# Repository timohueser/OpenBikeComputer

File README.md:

<div align="center">

# OpenBikeComputer

**An open-source GPS computer for bikepacking.**

[Live browser demo](https://openbikecomputer.com/#demo) ·
[Documentation](https://openbikecomputer.com/docs/software/architecture/) ·
[Contributing](.github/CONTRIBUTING.md)

</div>

> [!NOTE]
> This project is developed with extensive use of AI coding tools. Don't get out your "AI Slop"
> pitchforks just yet though. Any text you read in the software or documentation that sounds AI
> generated will be replaced once we get closer to releasing this project. The goal is that all
> user-facing text is 100% human-generated!

OpenBikeComputer is a fully open-source, bikepacking-focused GPS cycling computer.
The main features and capabilities we are aiming for are the following (roughly in order of importance):
- Reliable and simple map-based tracking and navigation
- Uploading a route from the companion app should work every time (no BLE connection issues, no unreasonably low limit on point count in GPX files etc.)
- No subscriptions or accounts required for any of the features of the device
- Long battery life, ideally 4+ days between recharges, if you need to recharge it should work reliably with dynamo hubs that provide 5V
- Helps you keep your phone in your pocket by providing all the info you frequently check on the bike:
    - POIS (Shops, water sources, campsites etc.) near you and along the route (including opening hours), with the ability to create a route there on the fly
    - And a fun one: Mountain peaks around you (PeakFinder style)

This repository contains all the software and hardware files needed to build the OBC and the goal is to eventually provide kits that allow you to build the OBC yourself. The project currently is an active prototype, not a finished product and you can read about the progress of development in our [Blog](https://openbikecomputer.com/blog/). Here are some peeks at the software and hardware designs:

<table>
  <tr>
    <td align="center" width="33%">
      
    </td>
    <td align="center" width="33%">
      
    </td>
    <td align="center" width="33%">
      
    </td>
  </tr>
  <tr>
    <td align="center"><sub>Follow the route on the offline map.</sub></td>
    <td align="center"><sub>Read your ride data as you go.</sub></td>
    <td align="center"><sub>See the climb ahead of you.</sub></td>
  </tr>
  <tr>
    <td align="center" width="33%">
      
    </td>
    <td align="center" width="33%">
      
    </td>
  </tr>
  <tr>
    <td align="center"><sub>Identify the peaks around you.</sub></td>
    <td align="center"><sub>Find a shop, and when it opens.</sub></td>
  </tr>
</table>

<table>
  <tr>
    <td align="center" width="50%">
      
    </td>
    <td align="center" width="50%">
      
    </td>
  </tr>
  <tr>
    <td align="center"><sub>Send a route to the bike computer.</sub></td>
    <td align="center"><sub>Bring the recorded ride back.</sub></td>
  </tr>
</table>

<table>
  <tr>
    <td align="center">
      
    </td>
  </tr>
  <tr>
    <td align="center"><sub>A concept render of the enclosure.</sub></td>
  </tr>
</table>

<table>
  <tr>
    <td align="center">
      
    </td>
  </tr>
  <tr>
    <td align="center"><sub>Five colourways under consideration.</sub></td>
  </tr>
</table>

## Try the simulator

The simulator is the best way to explore the project without hardware. It runs the real device
application in a desktop window and downloads the map, route, terrain, and ride data for the Grimsel
Pass demo on first use.

Install [Rust](https://rustup.rs/), Git, Python 3.14+, uv 0.8.17+ and just 1.57+:

```sh
git clone https://github.com/timohueser/OpenBikeComputer.git
cd OpenBikeComputer
cargo install just
just sim
```

First builds take a few minutes; fixture downloads are cached. `just --list` lists tasks;
`just --show TASK` shows a recipe. Run `./tools/obc setup` for the `obc` alias and completion.
See the [simulator guide](sim/desktop/README.md) for controls and rendering.

## Roadmap

This is the current direction, not a release schedule.

| Stage | Status |
| --- | --- |
| Shared application, offline maps, routing, ride recording | Available in the simulator and browser demo |
| iOS companion and BLE/USB transfer flows | Working with the development platform |
| nRF54LM20 development-kit prototype with the 240 × 320 reflective display | Running on hardware |
| Custom PCB and enclosure | In development |
| Integrated, field-tested bike computer | Next major milestone |
| Reproducible hardware build, assembly, and flashing guide | Planned when the custom hardware is ready |

## Current development platform

The hardware build uses the Nordic nRF54LM20 development kit and a Sharp LS021B7DD02 240 × 320
reflective memory LCD. It reads maps and routes from microSD and connects to the companion software
over BLE and USB. The custom PCB and enclosure are still under development. KiCad sources are in
[`hardware/`](hardware/README.md); CAD sources for the enclosure follow later.

## Repository layout

| Path | Purpose |
| --- | --- |
| `firmware/` | Device application, rendering, protocols, storage, board image, and bootloader |
| `host/` | Host tools, map bakers, fixtures, and test support |
| `planner/` | Router, build tools, service, search, and tile worker |
| `sim/` | Desktop, web and phone simulators, host core, replay, feeder and benchmarks |
| `builder/` | Web builder, Rust/WASM core, USB transport, presets, and server |
| `companion-ios/` | SwiftUI companion app and shared iOS package |
| `specs/` | Normative binary, wire, and vector contracts |
| `fixtures/` | Scenario registry, source provenance, and fixture builders |
| `data/` | External data sources with their licences, regions, and environments |
| `docs/` | Public documentation, website, and project blog |
| `hardware/` | KiCad schematics, PCB layouts, footprints, and component models |
| `tools/` | The `obc` command, repository tools, and verification console |

`Cargo.toml` lists the root workspace crates. The nRF54L board image,
bootloader, and sensor simulator are standalone Cargo roots. The
[architecture guide](https://openbikecomputer.com/docs/software/architecture/) explains the boundaries.

## Other open bike computers

OpenBikeComputer is not the only open source bike computer project! Here is a (non-exhaustive) list of some other cool ones this project is inspired by:

- [IceNav](https://github.com/jgauchia/IceNav-v3) — an ESP32-based GPS navigator with multi-GNSS
  support and both rendered and vector offline maps.
- [OpenTrailPaper](https://github.com/RaemondBW/OpenTrailPaper) — an ESP32-S3 e-paper computer
  with offline maps, ride recording, and an iOS companion.
- [Pedal Guru](https://github.com/juliannojungle/pedal.guru) — a work-in-progress bike computer
  project for Raspberry Pi, RP2040, and ESP32 platforms.
- [Pi Zero Bikecomputer](https://github.com/hishizuka/pizero_bikecomputer) — a Raspberry Pi GPS
  and ANT+ computer with offline maps, navigation, and FIT ride logging.
- [bike-computer-32](https://github.com/lspr98/bike-computer-32) — a low-cost ESP32-C3 mini-map
  with offline OpenStreetMap data, GNSS positioning, and GPX track overlays.

## Contributing

Contributions are always welcome! This project is in the very early stages and many things are still a little chaotic and not well documented in many areas. Code is written almost exclusively using AI coding agents, but all the hardware design is fully human-powered. Help on that front would be especially appreciated. Please just get in contact with me if you want to contribute.

## License

Software is available under [GPL-3.0-only](LICENSE), except `host/obc-data`, which is MIT OR
Apache-2.0 and depends on no GPL crate. Hardware design sources are available under
[CERN-OHL-S-2.0](hardware/LICENSE). Third-party notices are in
[the notice file](tools/licenses/THIRD-PARTY.md).

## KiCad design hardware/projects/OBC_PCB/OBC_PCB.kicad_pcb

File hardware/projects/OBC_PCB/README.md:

# OBC main board

Open `OBC_PCB.kicad_pro` in KiCad 10. Keep the project library tables with the files.
Run electrical checks from this directory:

```sh
kicad-cli sch erc --format json -o /tmp/obc-erc.json OBC_PCB.kicad_sch
kicad-cli pcb drc --schematic-parity --format json -o /tmp/obc-drc.json OBC_PCB.kicad_pcb
```

## Board GPIO map

This table describes the main PCB. The [firmware README](../../../firmware/obc-fw-nrf54l/README.md)
describes the development kit. Port the firmware pin assignments before running it on this board.
`LCD_*_MCU` is the net between U6 and its source resistor; `LCD_*` continues to J1.

| Device | Pad | GPIO | Signal | Connection |
| --- | --- | --- | --- | --- |
| U6 | 1 | P2.01 | SD_CLK | R9, 33 Ω at U6; fixed SD pin |
| U6 | 2 | P2.02 | SD_D0 | Fixed SD pin |
| U6 | 3 | P2.03 | SD_D2 | Fixed SD pin |
| U6 | 4 | P2.04 | SD_D1 | Fixed SD pin |
| U6 | 5 | P2.05 | SD_CMD | Fixed SD pin |
| U6 | 7 | P1.29 | COM_SOURCE |  |
| U6 | 8 | P1.30 | LCD_R0 | R69, 100 Ω at U6 |
| U6 | 9 | P1.31 | LCD_R1 | R70, 100 Ω at U6 |
| U6 | 10 | P1.00 | BUZZER_PWM |  |
| U6 | 11 | P1.01 | LCD_GSP | R77, 220 Ω at U6 |
| U6 | 12 | P1.02 | LCD_GEN | R78, 220 Ω at U6 |
| U6 | 13 | P1.03 | LCD_BSP | R80, 220 Ω at U6 |
| U6 | 14 | P1.04 | LCD_GCK | R76, 220 Ω at U6 |
| U6 | 15 | P1.05 | LCD_BCK | R75, 100 Ω at U6 |
| U6 | 16 | P1.06 | LCD_G0 | R71, 100 Ω at U6 |
| U6 | 22 | P1.07 | LCD_G1 | R72, 100 Ω at U6 |
| U6 | 23 | P1.08 | LCD_B0 | R73, 100 Ω at U6 |
| U6 | 24 | P1.09 | LCD_B1 | R74, 100 Ω at U6 |
| U6 | 25 | P0.03 | GPS_TXD | UARTE30 RX (module TX) |
| U6 | 26 | P0.04 | BTN_SELECT | GPIO SENSE wake |
| U6 | 27 | P0.06 | BTN_NEXT | GPIO SENSE wake |
| U6 | 28 | P0.07 | BTN_BACK | GPIO SENSE wake |
| U6 | 29 | P0.08 | PMIC_INT |  |
| U6 | 30 | P0.09 | GPS_RXD | UARTE30 TX (module RX) |
| U6 | 39 | P1.15 | BTN_PREV | GPIO SENSE wake |
| U6 | 40 | P1.16 | SDA | TWIM22 data |
| U6 | 41 | P1.18 | SCL | TWIM22 clock pin |
| U6 | 47 | P1.19 | ACC_INT1 | GPIO SENSE wake |
| U6 | 50 | P1.24 | LCD_INTB | R79, 220 Ω at U6 |
| U6 | 52 | P2.00 | SD_D3 | Fixed SD pin |
| U2 | 7 | GPIO0 | DISP_5V_EN |  |
| U2 | 8 | GPIO1 | PMIC_INT |  |
| U2 | 9 | GPIO2 | COM_EN |  |
| U2 | 10 | GPIO3 | LOUD |  |
| U2 | 11 | GPIO4 | DISP_DISCHARGE |  |

Use standard drive for the LCD outputs. Disable NFC through `NFCT.PADCONFIG` before
using GSP and GEN. Keep both low during reset. Set SCL and SDA on the same port.
Configure the crystal load capacitors and the internal DC/DC converter before use.
Program the bootloader through J5 before fitting the display.

For the LCD, measure 10–90% rise and fall times at J1. Target 25 ns or less;
the panel limit is 50 ns. The resistor values are initial values for board testing.
Check the image and GNSS reception while the display refreshes.

See Nordic's [port capabilities](https://docs.nordicsemi.com/r/bundle/ps_nrf54lm20a/page/gpio.html-concept_port_capabilities),
[clock-pin rules](https://docs.nordicsemi.com/r/bundle/ps_nrf54lm20a/page/chapters/pin.html-clock_pins)
and [GPIO electrical specification](https://docs.nordicsemi.com/r/bundle/ps_nrf54lm20a/page/elspec.html-unique_1225635930).

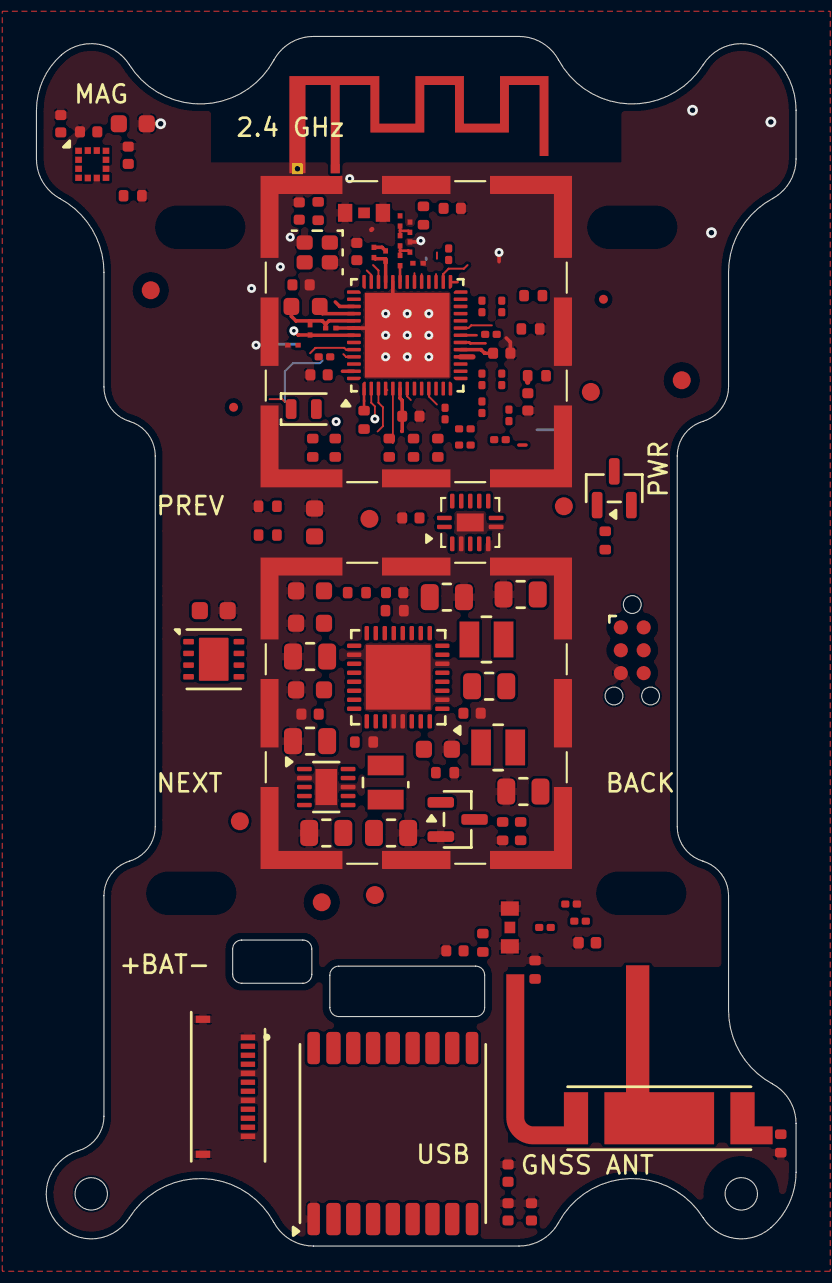
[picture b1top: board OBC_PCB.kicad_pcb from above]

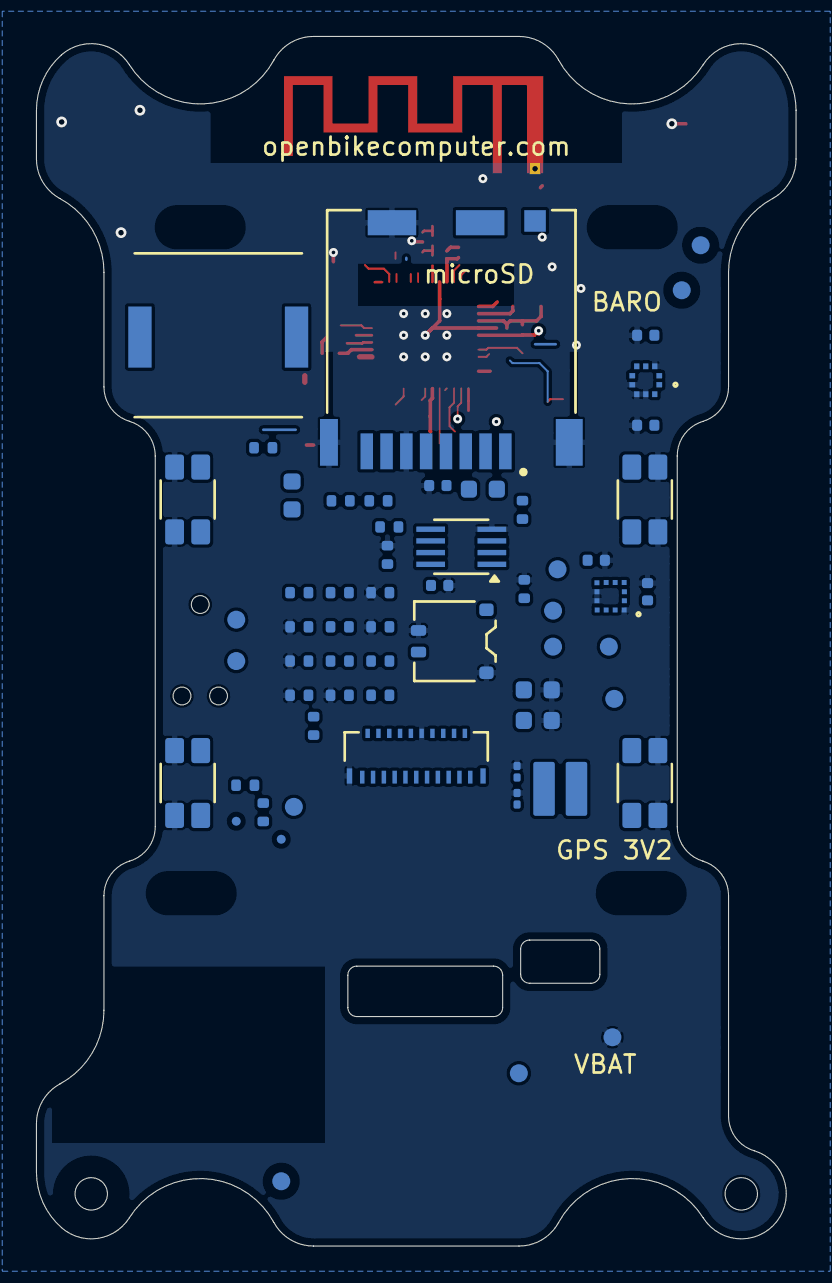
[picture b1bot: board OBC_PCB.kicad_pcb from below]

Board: 8 copper layers, 42.2 x 67.2 mm, 186 parts (61 on the bottom side), 115 nets.

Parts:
AE2: PCB MIFA; Texas_SWRA117D_2.4GHz_Right
ANT1: GGBLA.125.A; Taoglas_GGBLA125A_10x3.2mm_Corner
BZ1: CPT-9019A-SMT-TR
C1, C2, C3, C4, C5, C8: 10u; C_0805_2012Metric
C6, C14, C20, C44, C54: 1u; C_0603_1608Metric
C7, C16, C17, C22, C23, C24, C29, C30, C33, C34, C35, C36, C37, C38, C43, C52, C53: 100n; C_0402_1005Metric
C9, C10: 22u; C_0805_2012Metric
C11, C28: 2.2u; C_0402_1005Metric
C12: 4.7u; C_Nordic_0201_0603Metric
C13: 1p; C_Nordic_0201_0603Metric
C15, C39, C40, C49: 2.2u; C_0603_1608Metric
C21: 10u; C_0402_1005Metric
C25: 2.2u; C_Nordic_0201_0603Metric
C26: 4.7u; C_0402_1005Metric
C27: 10p; C_0201_0603Metric
C31: 47p; C_0201_0603Metric
C32: 4.3p; C_0201_0603Metric
C41, C51: 10u; C_0603_1608Metric
C42: 220n; C_0402_1005Metric
C45: 1.2p; C_Nordic_0201_0603Metric
C46: 1.5p; C_Nordic_0201_0603Metric
C47, C48, C50: tune (C0G); C_0402_1005Metric
C55: 3.9p; C_Nordic_0201_0603Metric
D1: BAS40-7-F; SOT-23
FID1, FID2, FID3, FID4, FID5, FID6: Fiducial_1mm_Mask2mm
FID7, FID8, FID9, FID10: Fiducial_0.5mm_Mask1mm
H1, H2: 1.8mm NPTH
H3, H4, H5, H6: Cradle 4.2x1.6mm NPTH
J1: LS021B7DD02; 5035662102
J2: DM3CS-SF; HRS_DM3CS-SF
J3: FH34SRJ-12S-0.5SH(50); Hirose_FH34SRJ_12S_0.5SH
J4: 1S Li-Po; JST_ACH_2pin
J5: TC2030-CTX-NL; Tag-Connect_TC2030-IDC-NL_2x03_P1.27mm_Vertical
J6: BACKLIGHT A/K - PROVISIONAL SOLDER; Backlight_Flex_Solder_2_P1.8mm_Provisional
J7, J8: RF coax pads; RF_Coax_Solder_GSG
L1, L2, L5: 2.2uH; Wurth_74404024022_2.5x2.0mm
L3: 4.7uH; L_0603_1608Metric
L4: 120R; L_Nordic_0201_0603Metric
L6: 1.0nH; L_Nordic_0201_0603Metric
L7: 3.9nH; L_0402_1005Metric
L8: 3.6nH; L_Nordic_0201_0603Metric
L9: 4.7nH; L_Nordic_0201_0603Metric
L10: 3.3nH; L_Nordic_0201_0603Metric
Q1: AO3400A; SOT-23
R1, R26, R27, R35, R39, R40, R50: 0R; R_0402_1005Metric
R2: 150k; R_0402_1005Metric
R3: 1M; R_0402_1005Metric
R4: 200R; R_0402_1005Metric
R5: 2.2R; R_0402_1005Metric
R9: 33R; R_0402_1005Metric
R20: 10k; R_0402_1005Metric
R23, R24: 4.7k; R_0402_1005Metric
R28, R29, R30, R31, R32, R34, R46: 47k; R_0402_1005Metric
R33, R41, R43: 470R; R_0402_1005Metric
R42, R44, R45, R47, R51, R52, R53, R54, R55, R56, R57, R58, R59, R60, R61, R62, R67: 100k; R_0402_1005Metric
R48, R49: 150R; R_0402_1005Metric
R63: 36.5k; R_0402_1005Metric
R64: 10.5k; R_0201_0603Metric
R65: 36.5k; R_0201_0603Metric
R66: 1k; R_0402_1005Metric
R68: 1k; R_0201_0603Metric
R69, R70, R71, R72, R73, R74, R75: 100; R_0201_0603Metric
R76, R77, R78, R79, R80: 220; R_0201_0603Metric
SH1, SH2: BMI-S-202-F-20-R; Laird_BMI-S-202-F-20_16.5mm
SW1: PREV; TL1016AAF220QG
SW2: NEXT; TL1016AAF220QG
SW3: SELECT / POWER; TL1016AAF220QG
SW4: BACK; TL1016AAF220QG
TP1: SHPHLD; TestPoint_Pad_D1.0mm
TP2: SAFEBOOT; TestPoint_Pad_D1.0mm
TP3: VBAT; TestPoint_Pad_D1.0mm
TP4: VSYS; TestPoint_Pad_D1.0mm
TP5: +3V2; TestPoint_Pad_D1.0mm
TP6: GND; TestPoint_Pad_D1.0mm
TP7: +3V2_GPS; TestPoint_Pad_D1.0mm
TP8: +3V3_SD; TestPoint_Pad_D1.0mm
TP9: COM_SOURCE; TestPoint_Pad_D1.0mm
TP10: +5V_DISP; TestPoint_Pad_D1.0mm
TP11: SCL; TestPoint_Pad_D1.0mm
TP12: SDA; TestPoint_Pad_D1.0mm
TP13: USB_VBUS; TestPoint_Pad_D1.0mm
TP14: VCOM; TestPoint_Pad_D1.0mm
TP15: VA; TestPoint_Pad_D1.0mm
U1: MAX-F11N; ublox_MAX_F11N_Provisional
U2: nPM1300-QEAA; QFN-32-1EP_5x5mm_P0.5mm_EP3.6x3.6mm
U3: BMA400; QFN_BMA400_BOS
U4: LIS2MDL; LGA-12_2x2mm_P0.5mm
U5: BMP581
U6: nRF54LM20A-QGAA; VQFN-52-1EP_6x6mm_P0.4mm_EP4.7x4.7mm
U7: TPS63900DSKR; WSON-10-1EP_2.5x2.5mm_P0.5mm_EP1.2x2mm
U8: SN74LVC02ABQAR; DHWQFN-14-1EP_2.5x3mm_P0.5mm_EP1x1.5mm
U9: LP5810BDSDR; LP5810_DSD0008B
U10: SN74LVC2G00DCTR; SSOP-8_2.95x2.8mm_P0.65mm
Y1: 32MHz; Crystal_SMD_2016-4Pin_2.0x1.6mm
Y3: 32.768kHz; Crystal_SMD_2012-2Pin_2.0x1.2mm

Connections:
+3V2: C2.1, C7.1, C21.1, C22.1, C23.1, C24.1, C30.1, C33.1, C34.1, C35.1, C36.1, C37.1, C38.1, C39.1, C49.1, C51.1, C52.1, C53.1, C54.1, J1.13 (VDD1), J5.1 (VTref), L2.1, R20.1, R23.1, R24.1, TP5.1 (1_1), U1.6 (V_BCKP), U2.12 (VDDIO), U2.30 (LSIN2/VINLDO2), U2.32 (VOUT2), U3.3 (VDDIO), U3.7 (VDD), U3.10 (CSB), U4.3 (~CS), U4.9 (Vdd), U4.10 (Vdd_IO), U5.1 (VDDIO), U5.5 (ADDR), U5.6 (CSB), U5.10 (VDD), U6.6 (VDD), U6.42 (VDD), U6.51 (VDD), U8.14 (VCC), U9.1 (VCC), U10.2, U10.8 (VCC)
+3V2_GPS: C20.1, C28.1, C29.1, TP7.1 (1_1), U1.7 (V_IO), U1.8 (VCC), U2.31 (LSOUT2/VOUTLDO2)
+3V3_SD: C1.1, C41.1, C43.1, J2.4 (VDD), L1.1, R28.1, R29.1, R30.1, R31.1, R32.1, TP8.1 (1_1), U2.1 (VOUT1)
+5V_DISP: C9.1, C10.1, C40.1, J1.21 (VDD2), J6.1, R66.1, TP10.1 (1_1), U7.6 (VOUT)
/ACC_INT1: U3.5 (INT1), U6.47 (P1.19)
/BTN_BACK: SW4.1, U6.28 (P0.07)
/BTN_NEXT: SW2.1, U6.27 (P0.06)
/BTN_PREV: SW1.1, U6.39 (P1.15)
/BTN_SELECT: R43.2, U6.26 (P0.04)
/BUZZER_PWM: R44.1, U6.10 (P1.00), U10.1
/COM_EN: R47.1, U2.9 (GPIO2), U8.5
/COM_SOURCE: R46.1, TP9.1 (1_1), U6.7 (P1.29), U8.2, U8.11
/Display/BL_K: J6.2, U9.8 (OUT0)
/GNSS/GNSS_FTE1: ANT1.2 (FTE), R26.1
/GNSS/GNSS_FTE2: ANT1.3 (FTE), R27.1
/GNSS/GNSS_RF_FEED: ANT1.1, C27.2, L7.1
/GNSS/GNSS_RF_IN: C50.1, R40.1, U1.11 (RF_IN)
/GNSS/GNSS_RF_MATCH: C27.1, C31.2, C32.1
/GNSS/GNSS_RF_TEST: C31.1, J8.1 (In), R40.2
/GPS_RXD: U1.3 (RXD), U6.30 (P0.09)
/GPS_TXD: U1.2 (TXD), U6.25 (P0.03)
/LCD_B0: J1.5 (B0), R55.1, R73.2
/LCD_B0_MCU: R73.1, U6.23 (P1.08)
/LCD_B1: J1.4 (B1), R56.1, R74.2
/LCD_B1_MCU: R74.1, U6.24 (P1.09)
/LCD_BCK: J1.10 (BCK), R62.1, R75.2
/LCD_BCK_MCU: R75.1, U6.15 (P1.05)
/LCD_BSP: J1.11 (BSP), R61.1, R80.2
/LCD_BSP_MCU: R80.1, U6.13 (P1.03)
/LCD_G0: J1.7 (G0), R53.1, R71.2
/LCD_G0_MCU: R71.1, U6.16 (P1.06)
/LCD_G1: J1.6 (G1), R54.1, R72.2
/LCD_G1_MCU: R72.1, U6.22 (P1.07)
/LCD_GCK: J1.18 (GCK), R59.1, R76.2
/LCD_GCK_MCU: R76.1, U6.14 (P1.04)
/LCD_GEN: J1.17 (GEN), R58.1, R78.2
/LCD_GEN_MCU: R78.1, U6.12 (P1.02)
/LCD_GSP: J1.19 (GSP), R57.1, R77.2
/LCD_GSP_MCU: R77.1, U6.11 (P1.01)
/LCD_INTB: J1.16 (INTB), R60.1, R79.2
/LCD_INTB_MCU: R79.1, U6.50 (P1.24)
/LCD_R0: J1.9 (R0), R51.1, R69.2
/LCD_R0_MCU: R69.1, U6.8 (P1.30)
/LCD_R1: J1.8 (R1), R52.1, R70.2
/LCD_R1_MCU: R70.1, U6.9 (P1.31)
/PMIC_INT: U2.8 (GPIO1), U6.29 (P0.08)
/Power Management/DISP_5V_EN: R3.1, U2.7 (GPIO0), U7.1 (EN)
/Power Management/DISP_DISCHARGE: Q1.1 (G), R67.1, U2.11 (GPIO4)
/Power Management/LOUD: R45.1, U2.10 (GPIO3), U10.6
/Power Management/SHPHLD: D1.3 (K), SW3.1, TP1.1 (1_1), U2.15 (SHPHLD)
/Radio/ANT: L8.1, U6.34 (ANT)
/Radio/RF24_FEED: AE2.1 (FEED), C48.1, R35.2
/Radio/RF24_LPF: L10.2, R39.1
/Radio/RF24_M1: C45.1, L8.2, L9.1
/Radio/RF24_M2: C46.1, L9.2, L10.1
/Radio/RF24_TEST: C47.1, J7.1 (In), R35.1, R39.2
/SCL: R23.2, TP11.1 (1_1), U2.14 (SCL), U3.12 (SCL), U4.1 (SCL/SPC), U5.2 (SCL), U6.41 (P1.18), U9.3 (SCL)
/SDA: R24.2, TP12.1 (1_1), U2.13 (SDA), U3.2 (SDA), U4.4 (SDA/SDI/SDO), U5.4 (SDA), U6.40 (P1.16), U9.4 (SDA)
/SD_CLK_RAW: R9.1, U6.1 (P2.01)
/SD_CMD: J2.3 (CMD), R28.2, U6.5 (P2.05)
/SD_D0: J2.7 (DAT0), R29.2, U6.2 (P2.02)
/SD_D1: J2.8 (DAT1), R30.2, U6.4 (P2.04)
/SD_D2: J2.1 (DAT2), R31.2, U6.3 (P2.03)
/SD_D3: J2.2 (CD/DAT3), R32.2, U6.52 (P2.00)
/SWDCLK: J5.4 (SWCLK), U6.31 (SWDCLK)
/SWDIO: J5.2 (SWDIO), U6.32 (SWDIO)
/Storage/SD_CLK: J2.5 (CLK), R9.2
/USB_D+: J3.6, U6.19 (D+)
/USB_D-: J3.7, U6.20 (D-)
/USB_VBUS: C6.1, R5.1, TP13.1 (1_1), U2.22 (VBUSOUT)
/nRESET: J5.3 (~RESET), R20.2, R68.2
GND: AE2.2 (GND), C1.2, C2.2, C3.2, C4.2, C5.2, C6.2, C7.2, C8.2, C9.2, C10.2, C11.2, C12.2, C14.2, C15.2, C16.2, C17.2, C20.2, C21.2, C22.2, C23.2, C24.2, C25.2, C26.2, C28.2, C29.2, C30.2, C32.2, C33.2, C34.2, C35.2, C36.2, C37.2, C38.2, C39.2, C40.2, C41.2, C42.2, C43.2, C45.2, C46.2, C47.2, C48.2, C49.2, C50.2, C51.2, C52.2, C53.2, C54.2, C55.2, J1.12 (VSS), J1.MP1, J1.MP2, J2.6 (VSS), J2.S1 (GND), J2.S2 (GND), J2.S3 (GND), J2.S5 (GND), J3.1, J3.5, J3.8, J3.12, J3.MP, J4.2 (-), J4.MP, J5.5 (GND), J7.2 (Ext), J8.2 (Ext), L7.2, Q1.2 (S), R1.2, R2.2, R3.2, R4.1, R26.2, R27.2, R42.2, R44.2, R45.2, R46.2, R47.2, R51.2, R52.2, R53.2, R54.2, R55.2, R56.2, R57.2, R58.2, R59.2, R60.2, R61.2, R62.2, R63.2, R64.2, R65.2, R67.2, SH1.1, SH2.1, SW1.2, SW2.2, SW3.2, SW4.2, TP6.1 (1_1), U1.1 (GND), U1.10 (GND), U1.12 (GND), U2.2 (PVSS1), U2.6 (PVSS2), U2.18 (NTC), U2.28 (LSIN1/VINLDO1), U2.29 (LSOUT1(GND)), U2.33 (AVSS), U3.1 (ADDR), U3.8 (GNDIO), U3.9 (GND), U4.6 (GND), U4.8 (GND), U5.3 (VSS), U5.7 (INT(GND)), U5.8 (VSS), U5.9 (VSS), U6.35 (VSS), U6.45 (VSS), U6.53 (VSS), U7.2 (SEL), U7.8 (GND), U7.11 (GND), U8.3, U8.6, U8.7 (GND), U8.15 (EP), U9.2 (SYNC), U9.9 (GND), U10.4 (GND), Y1.2 (G), Y1.4 (G)
unnamed: BZ1.1, R33.2, R34.1
unnamed: BZ1.2, C44.2, R34.2
unnamed: C44.1, R41.2
unnamed: D1.1 (A), R43.1
unnamed: J1.14 (VA), R49.2, TP15.1 (1_1)
unnamed: J1.15 (VB), R50.2
unnamed: J1.2 (VCOM), R48.2, R50.1, TP14.1 (1_1)
unnamed: J3.4, U2.23 (CC1)
unnamed: J3.9, U2.24 (CC2)
unnamed: Q1.3 (D), R66.2
unnamed: R33.1, U10.5, U10.7
unnamed: R41.1, U10.3
unnamed: R48.1, U8.10
unnamed: R49.1, U8.13
unnamed: TP2.1 (1_1), U1.18 (~SAFEBOOT)
unnamed: L1.2, U2.3 (SW1)
unnamed: L2.2, U2.5 (SW2)
unnamed: R1.1, U2.17 (VSET1)
unnamed: R2.1, U2.16 (VSET2)
unnamed: C42.1, U4.5 (C1)
unnamed: R42.1, U4.7 (DRDY)
unnamed: L3.1, U6.43 (DCC)
unnamed: C13.1, C25.1, L4.2, L6.1, U6.46 (DECA)
unnamed: C12.1, L3.2, L4.1, U6.44 (DECD)
unnamed: C13.2, L6.2, U6.36 (DECRF)
unnamed: C11.1, U6.18 (DECUSB)
unnamed: U6.48 (P1.20), Y3.1
unnamed: U6.49 (P1.21), Y3.2
unnamed: R4.2, U6.21 (TXRTUNE)
unnamed: C26.1, R5.2, U6.17 (VBUS)
unnamed: U6.37 (XC1), Y1.1
unnamed: U6.38 (XC2), Y1.3
unnamed: C55.1, R68.1, U6.33 (~RESET)
unnamed: R63.1, U7.3 (CFG1)
unnamed: R64.1, U7.4 (CFG2)
unnamed: R65.1, U7.5 (CFG3)
unnamed: L5.1, U7.9 (LX1)
unnamed: L5.2, U7.7 (LX2)
unnamed: U8.1, U8.8
unnamed: U8.4, U8.9, U8.12
VBAT: C15.1, J4.1 (+), TP3.1 (1_1), U2.19 (VBAT)
VBUS: C14.1, J3.2, J3.3, J3.10, J3.11, U2.21 (VBUS)
VSYS: C3.1, C4.1, C5.1, C8.1, C16.1, C17.1, TP4.1 (1_1), U2.4 (PVDD), U2.20 (VSYS), U7.10 (VIN)

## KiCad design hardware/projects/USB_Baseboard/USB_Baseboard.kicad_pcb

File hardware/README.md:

# Hardware BOM

Open either project's `.kicad_pro` in KiCad 10. In the Schematic Editor, open
**Edit Symbol Fields** and select **OBC specifications**. Edit component ratings,
manufacturer part numbers, supplier links and prices there. Save the schematic.
The fields are hidden on the drawing to keep it readable.

For a board CSV, open **Generate Bill of Materials**, select **OBC purchasing**
and the **CSV** format, then click **Export**. This preset excludes DNP parts
and symbols marked **Exclude from bill of materials**. It includes shield lids.
Keep board exclusion separate from BOM exclusion.

For a combined main-board and USB-board report, run from the checkout root:

```sh
python3 hardware/bom.py
open target/bom/index.html
```

Python uses the standard library. Install KiCad 10. The script finds `kicad-cli`
on PATH or in the macOS application. Use `--kicad-cli PATH` to override it.
Use `--output PATH` to select the output directory.
Add `--schematics` to export all schematic sheets as one PDF per board.

The output contains each native board CSV, `purchasing.csv`, and `index.html`.
The combined CSV retains the exported specification fields. Edit the schematic
fields, then run the command again. Generated files are not the source of truth.

| Field | Format |
| --- | --- |
| Manufacturer / MPN | Exact manufacturer and order code; use the same spelling on each instance |
| Mouser / DigiKey | Product page for that order code |
| Alternate MPN / Alternate source | Separate order code, such as another reel size |
| Price source | Supplier page used for the recorded prices |
| Price breaks EUR | Quantity and EUR per part, excluding VAT: `1:0.12;10:0.08;1000:0.04` |
| Price breaks EUR, whole reels | Add an order multiple: `1000@1000:0.03` |
| Price checked | ISO date when the supplier prices were checked |
| Selection notes | Electrical or mechanical checks still required |
| Sourcing notes | Stock, delivery, packaging or quote limits |

The two build sizes are 10 and 1,000 devices. Each device has one main board and
one USB daughterboard. Prices use the total quantity of each MPN across both
boards. A reel price applies only when that quantity is a multiple of the reel
size. Where a higher price break is unavailable, the last recorded eligible
break gives a conservative estimate. Conflicting prices on the same MPN stop
the export. Blank prices remain unknown and are excluded from the subtotal.

Supplier prices and delivery estimates can change. Indexed supplier pages can
lag the live catalogue. Refresh prices and check stock before purchase. Edit
all instances of the same MPN together in KiCad. Clear all price fields when
you change an MPN until you have a quote for the new part.

Check capacitor DC-bias limits and total rail capacitance before release.
Review RF tuning and provisional footprints in the exported notes. This report
does not qualify the circuit or layout for production.

The report covers schematic components. It excludes bare PCBs, the USB flex,
display, battery, SD card, enclosure, assembly, shipping, VAT and extra parts.
The docs site publishes the report, CSV files and schematic PDFs from `develop`.
Hardware changes trigger the site build. To preview the published page locally,
run `python3 docs/build_docs.py --hardware --check-links`. See
[the docs preview instructions](../docs/README.md#check-and-preview).

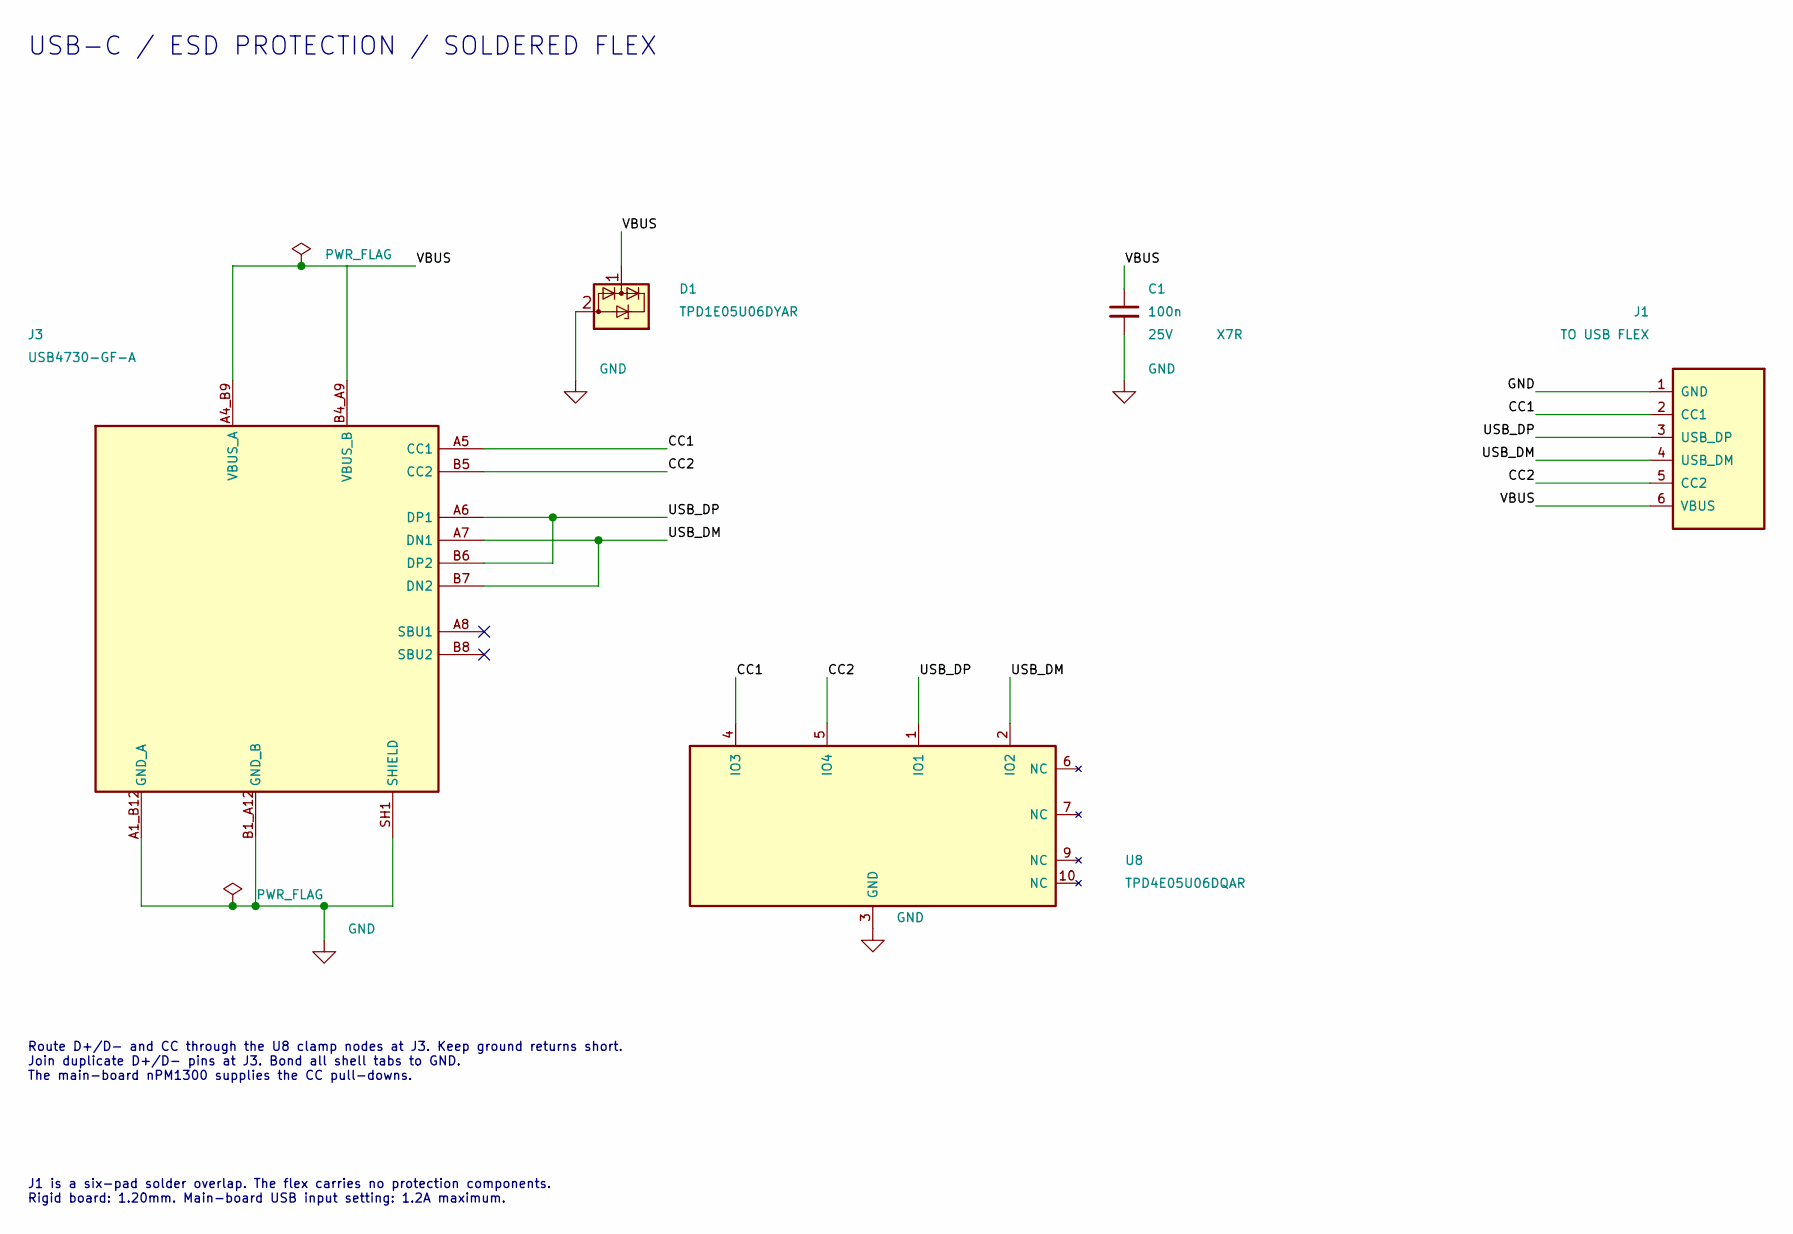
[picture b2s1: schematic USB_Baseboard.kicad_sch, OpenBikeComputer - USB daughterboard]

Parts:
C1: 100n; C_0402_1005Metric; Voltage 25V; Tolerance 10%
D1: TPD1E05U06DYAR; D_SOD-523; MPN TPD1E05U06DYAR
J1: TO USB FLEX; USB_Flex_Solder_6
J3: USB4730-GF-A; GCT_USB4730-GF-A; PARTREV A
U8: TPD4E05U06DQAR; TI_DQA0010A_USON-10_2.5x1.0mm_P0.5mm; MPN TPD4E05U06DQAR

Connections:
/CC1: J1.2 (CC1), J3.A5 (CC1), U8.4 (IO3)
/CC2: J1.5 (CC2), J3.B5 (CC2), U8.5 (IO4)
/USB_DM: J1.4 (USB_DM), J3.A7 (DN1), J3.B7 (DN2), U8.2 (IO2)
/USB_DP: J1.3 (USB_DP), J3.A6 (DP1), J3.B6 (DP2), U8.1 (IO1)
/VBUS: C1.1, D1.1 (I/O), J1.6 (VBUS), J3.A4_B9 (VBUS_A), J3.B4_A9 (VBUS_B)
GND: C1.2, D1.2 (GND), J1.1 (GND), J3.A1_B12 (GND_A), J3.B1_A12 (GND_B), J3.SH1 (SHIELD), J3.SH2 (SHIELD), J3.SH3 (SHIELD), J3.SH4 (SHIELD), U8.3 (GND), U8.8 (GND)

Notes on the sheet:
USB-C / ESD PROTECTION / SOLDERED FLEX
Route D+/D- and CC through the U8 clamp nodes at J3. Keep ground returns short. Join duplicate D+/D- pins at J3. Bond all shell tabs to GND. The main-board nPM1300 supplies the CC pull-downs.
J1 is a six-pad solder overlap. The flex carries no protection components. Rigid board: 1.20mm. Main-board USB input setting: 1.2A maximum.

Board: 2 copper layers, 5 parts (3 on the bottom side), 6 nets, no tracks yet.

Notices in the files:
README.md:
Software: GPL-3.0-only
Hardware: CERN-OHL-S-2.0
parts and their libraries:
License: CERN-OHL-P-2.0; hardware/libraries/LICENSE.nordic-lib-kicad
